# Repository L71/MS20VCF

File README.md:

# MS20VCF
Korg MS20 style VCF eurorack module

8HP Eurorack module based on this schematic: http://electro-music.com/wiki/pmwiki.php?n=Schematics.KorgLateMS20Filter

See also https://l71.github.io/ for more info.

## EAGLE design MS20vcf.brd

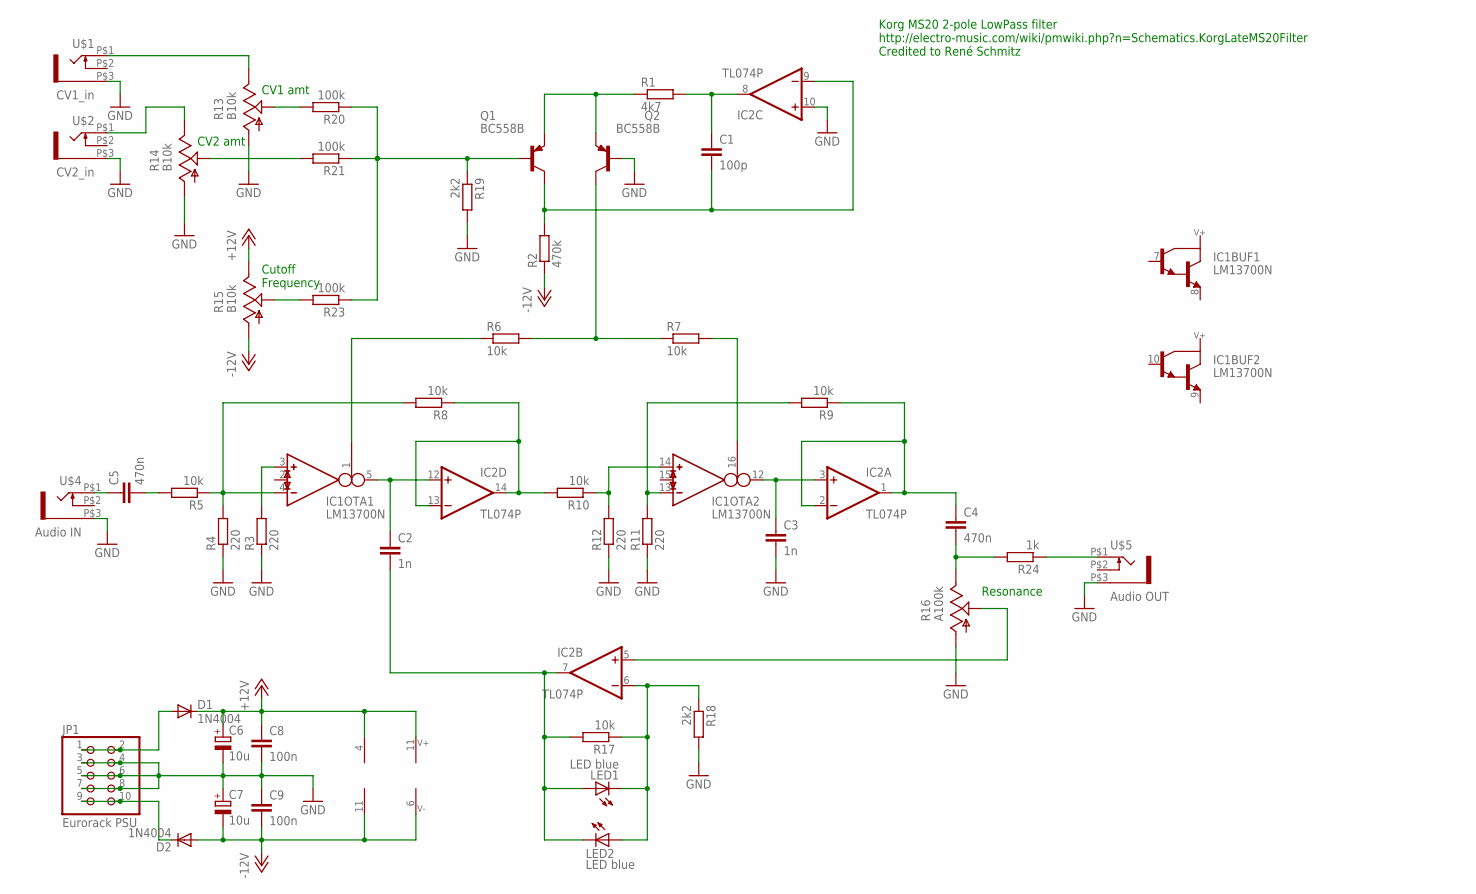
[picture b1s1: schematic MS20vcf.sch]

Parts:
C1: 100p; C025-025X050
C2, C3: 1n; C050-025X075
C4, C5: 470n; C050-025X075
C6, C7: 10u; E2,5-5
C8, C9: 100n; C025-025X050
D1, D2: 1N4004; D-7.5
IC1: LM13700N; DIL16
IC2: TL074P; DIL14
JP1: Eurorack PSU; 2X05
LED1, LED2: LED blue; LED3MM
Q1, Q2: BC558B; TO92-EBC
R1: 4k7; 0207/2V
R2: 470k; 0207/2V
R3, R4, R11, R12: 220; 0207/2V
R5, R6, R7, R8, R9, R10, R17: 10k; 0207/2V
R13, R14, R15: B10k; ALPS_POT_VERTICAL
R16: A100k; ALPS_POT_VERTICAL
R18, R19: 2k2; 0207/2V
R20, R21, R23: 100k; 0207/2V
R24: 1k; 0207/2V
U$1: CV1_in; WQP-PJ301M-12_JACK
U$2: CV2_in; WQP-PJ301M-12_JACK
U$4: Audio IN; WQP-PJ301M-12_JACK
U$5: Audio OUT; WQP-PJ301M-12_JACK

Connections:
+12V: C6.+, C8.1, D1.C, IC1.11 (V+), IC2.4 (V+), R15.P$1 (E)
-12V: C7.-, C9.2, D2.A, IC1.6 (V-), IC2.11 (V-), R2.1, R15.P$3 (A)
GND: C3.2, C6.-, C7.+, C8.2, C9.1, IC2.10 (+IN), JP1.3, JP1.4, JP1.5, JP1.6, JP1.7, JP1.8, Q2.B, R3.1, R4.1, R11.1, R12.1, R13.P$3 (A), R14.P$3 (A), R16.P$3 (A), R18.2, R19.2, U$1.P$3 (1), U$2.P$3 (1), U$4.P$3 (1), U$5.P$3 (1)
unnamed: C1.1, IC2.8 (OUT), R1.2
unnamed: Q1.E, Q2.E, R1.1
unnamed: C1.2, IC2.9 (-IN), Q1.C, R2.2
unnamed: Q2.C, R6.2, R7.1
unnamed: IC1.1 (I_BIAS), R6.1
unnamed: IC1.16 (I_BIAS), R7.2
unnamed: C2.1, IC1.5 (OUT), IC2.12 (+IN)
unnamed: C3.1, IC1.12 (OUT), IC2.3 (+IN)
unnamed: IC1.13 (IN_N), R9.2, R11.2
unnamed: IC1.3 (IN_P), R3.2
unnamed: IC1.4 (IN_N), R4.2, R5.1, R8.2
unnamed: IC2.13 (-IN), IC2.14 (OUT), R8.1, R10.2
unnamed: IC1.14 (IN_P), R10.1, R12.2
unnamed: IC2.6 (-IN), LED1.K (C), LED2.A, R17.1, R18.1
unnamed: C4.1, IC2.1 (OUT), IC2.2 (-IN), R9.1
unnamed: C5.2, R5.2
unnamed: C4.2, R16.P$1 (E), R24.2
unnamed: IC2.5 (+IN), R16.P$2 (S)
unnamed: C2.2, IC2.7 (OUT), LED1.A, LED2.K (C), R17.2
unnamed: Q1.B, R19.1, R20.1, R21.1, R23.1
unnamed: R15.P$2 (S), R23.2
unnamed: R13.P$1 (E), U$1.P$1 (2)
unnamed: R14.P$2 (S), R21.2
unnamed: R13.P$2 (S), R20.2
unnamed: R14.P$1 (E), U$2.P$1 (2)
unnamed: C5.1, U$4.P$1 (2)
unnamed: R24.1, U$5.P$1 (2)
unnamed: D1.A, JP1.1, JP1.2
unnamed: D2.C, JP1.9, JP1.10

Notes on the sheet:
Resonance
CV2 amt
CV1 amt
Cutoff Frequency
Korg MS20 2-pole LowPass filter http://electro-music.com/wiki/pmwiki.php?n=Schematics.KorgLateMS20Filter Credited to René Schmitz

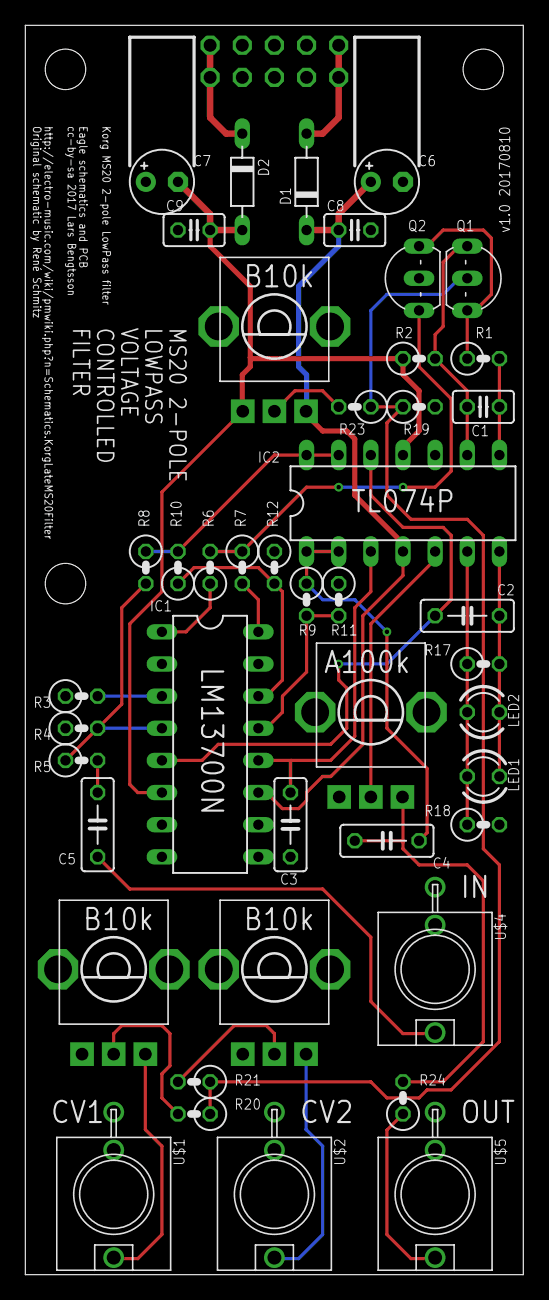
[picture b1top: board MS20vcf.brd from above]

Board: 2 copper layers, 39.4 x 98.7 mm, 45 parts (1 on the bottom side), 32 nets.

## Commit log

2017-08-26 Initial commit. Prototype built OK.
2017-08-29 Moved C3 to clear potentiometer, added value labels to potentiometers.
2019-04-27 Moved transistor pair closer.

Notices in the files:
MS20vcf.brd:
cc-by-sa 2017 Lars Bengtsson
